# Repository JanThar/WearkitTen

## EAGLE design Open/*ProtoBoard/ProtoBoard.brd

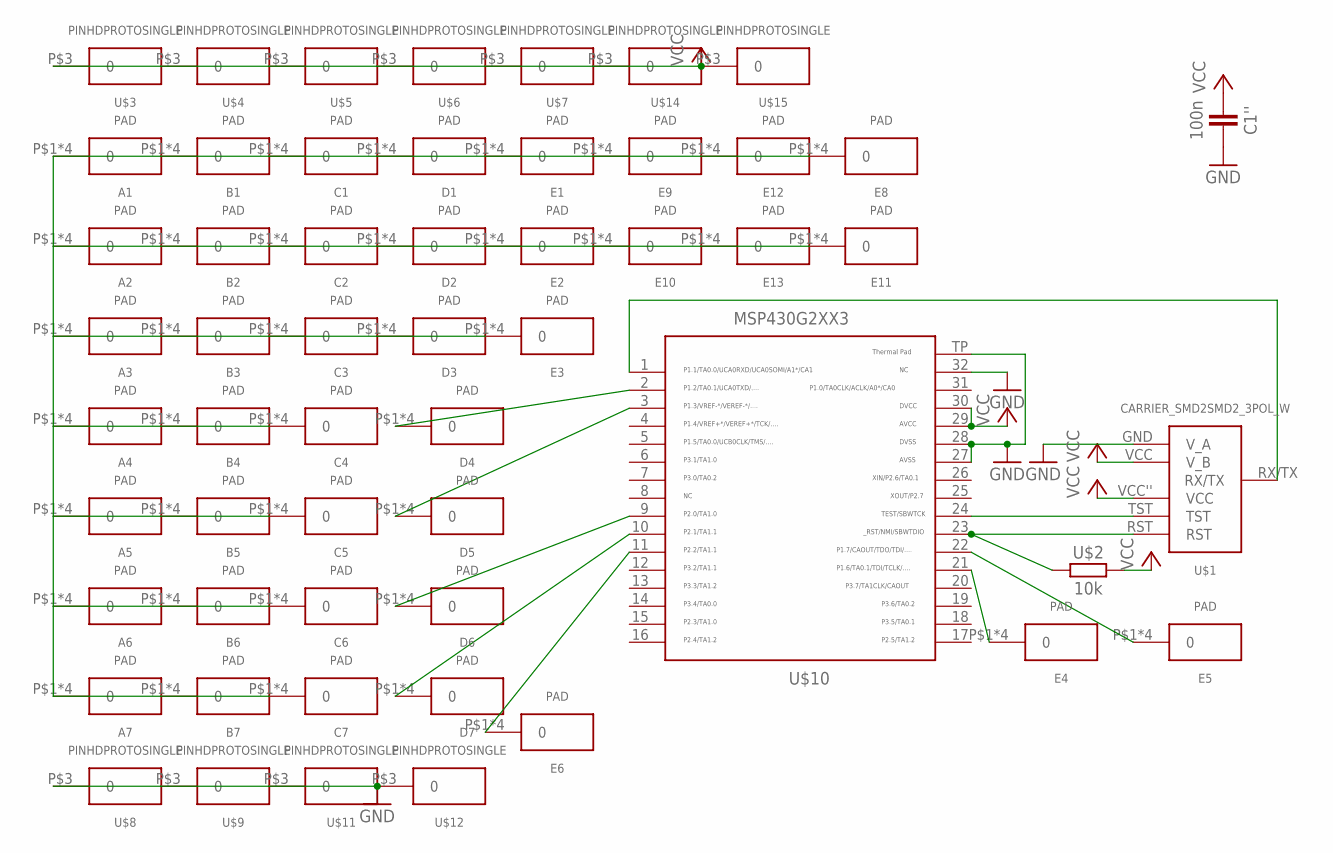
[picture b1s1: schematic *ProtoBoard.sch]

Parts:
A1, A2, A3, A4, A5, A6, A7: PAD; PROTPAD
B1, B2, B3, B4, B5, B6, B7: PAD; PROTPAD
C1, C2, C3, C4, C5, C6, C7: PAD; PROTPAD
C1'': 100n; 603
D1, D2, D3, D4, D5, D6, D7: PAD; PROTPAD
E1, E2, E3, E4, E5, E6, E8, E9, E10, E11, E12, E13: PAD; PROTPAD
U$1: CARRIER_SMD2SMD2_3POL_W; CARRIER_SMD2_WIDE_3POL
U$2: 10k; 603
U$3, U$4, U$5, U$6, U$7, U$8, U$9, U$11, U$12, U$14, U$15: PINHDPROTOSINGLE; PROTOPADSINGLE
U$10: MSP430G2553; QFN32

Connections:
GND: C1''.2, U$1.GND (V_A), U$8.P$3, U$9.P$3, U$10.27, U$10.28, U$10.32, U$10.TP, U$11.P$3, U$12.P$3
unnamed: A1.P$1, A1.P$2, A1.P$3, A1.P$4, A2.P$1, A2.P$2, A2.P$3, A2.P$4, A3.P$1, A3.P$2, A3.P$3, A3.P$4, A4.P$1, A4.P$2, A4.P$3, A4.P$4, A5.P$1, A5.P$2, A5.P$3, A5.P$4, A6.P$1, A6.P$2, A6.P$3, A6.P$4, A7.P$1, A7.P$2, A7.P$3, A7.P$4, B1.P$1, B1.P$2, B1.P$3, B1.P$4, B2.P$1, B2.P$2, B2.P$3, B2.P$4, B3.P$1, B3.P$2, B3.P$3, B3.P$4, B4.P$1, B4.P$2, B4.P$3, B4.P$4, B5.P$1, B5.P$2, B5.P$3, B5.P$4, B6.P$1, B6.P$2, B6.P$3, B6.P$4, B7.P$1, B7.P$2, B7.P$3, B7.P$4, C1.P$1, C1.P$2, C1.P$3, C1.P$4, C2.P$1, C2.P$2, C2.P$3, C2.P$4, C3.P$1, C3.P$2, C3.P$3, C3.P$4, C4.P$1, C4.P$2, C4.P$3, C4.P$4, C5.P$1, C5.P$2, C5.P$3, C5.P$4, C6.P$1, C6.P$2, C6.P$3, C6.P$4, C7.P$1, C7.P$2, C7.P$3, C7.P$4, D1.P$1, D1.P$2, D1.P$3, D1.P$4, D2.P$1, D2.P$2, D2.P$3, D2.P$4, D3.P$1, D3.P$2, D3.P$3, D3.P$4, E1.P$1, E1.P$2, E1.P$3, E1.P$4, E2.P$1, E2.P$2, E2.P$3, E2.P$4, E3.P$1, E3.P$2, E3.P$3, E3.P$4, E8.P$1, E8.P$2, E8.P$3, E8.P$4, E9.P$1, E9.P$2, E9.P$3, E9.P$4, E10.P$1, E10.P$2, E10.P$3, E10.P$4, E11.P$1, E11.P$2, E11.P$3, E11.P$4, E12.P$1, E12.P$2, E12.P$3, E12.P$4, E13.P$1, E13.P$2, E13.P$3, E13.P$4
unnamed: U$1.TST, U$10.24
unnamed: U$1.RST, U$2.1, U$10.23
unnamed: D4.P$1, D4.P$2, D4.P$3, D4.P$4, U$10.2
unnamed: D5.P$1, D5.P$2, D5.P$3, D5.P$4, U$10.3
unnamed: E5.P$1, E5.P$2, E5.P$3, E5.P$4, U$10.22
unnamed: E4.P$1, E4.P$2, E4.P$3, E4.P$4, U$10.21
unnamed: U$1.RX/TX, U$10.1
unnamed: D6.P$1, D6.P$2, D6.P$3, D6.P$4, U$10.9
unnamed: D7.P$1, D7.P$2, D7.P$3, D7.P$4, U$10.10
unnamed: E6.P$1, E6.P$2, E6.P$3, E6.P$4, U$10.11
VCC: C1''.1, U$1.VCC (V_B), U$1.VCC'' (VCC), U$2.2, U$3.P$3, U$4.P$3, U$5.P$3, U$6.P$3, U$7.P$3, U$10.29, U$10.30, U$14.P$3, U$15.P$3

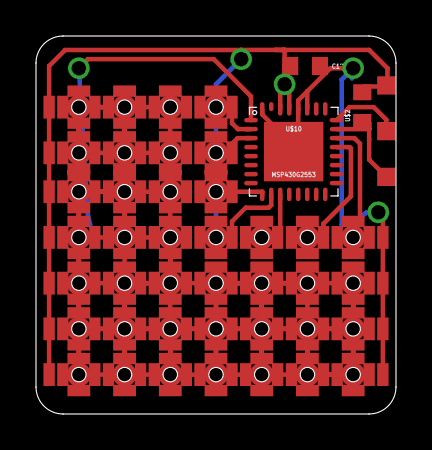
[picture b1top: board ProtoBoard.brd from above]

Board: 2 copper layers, 20.0 x 21.0 mm, 55 parts (0 on the bottom side), 13 nets.

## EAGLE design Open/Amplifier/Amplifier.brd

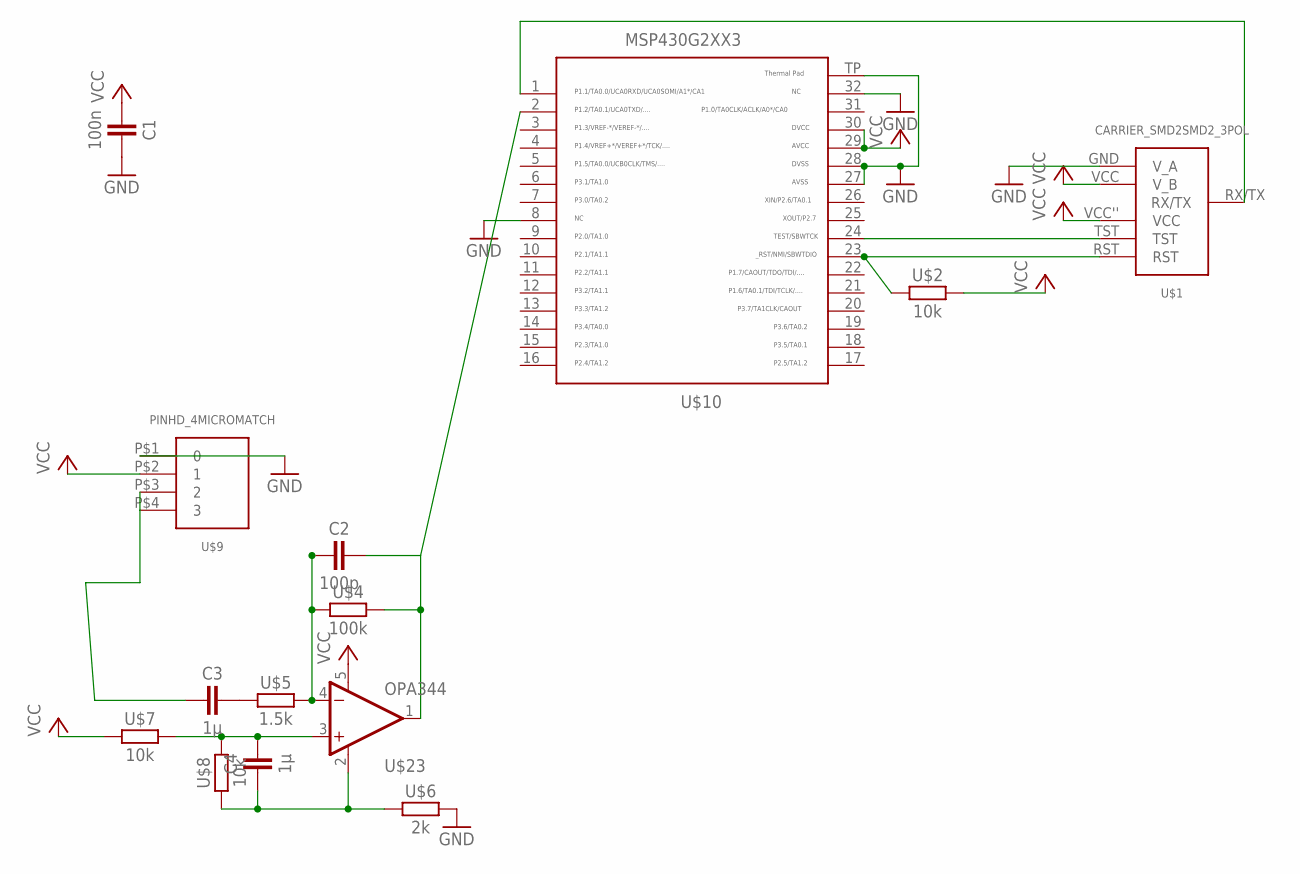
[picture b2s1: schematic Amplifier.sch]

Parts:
C1: 100n; 603
C2: 100p; 603
C3, C4: 1µ; 603
U$1: CARRIER_SMD2SMD2_3POL; CARRIER_SMD2_3POL
U$2, U$7, U$8: 10k; 603
U$4: 100k; 603
U$5: 1.5k; 603
U$6: 2k; 603
U$9: PINHD_4MICROMATCH; MICROMATCH4P0L
U$10: MSP430G2553; QFN32
U$23: OPA344; SOT23-5

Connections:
GND: C1.2, U$1.GND (V_A), U$6.2, U$9.P$1 (0), U$10.8, U$10.27, U$10.28, U$10.32, U$10.TP
unnamed: U$1.TST, U$10.24
unnamed: U$1.RST, U$2.1, U$10.23
unnamed: U$1.RX/TX, U$10.1
unnamed: C2.1, U$4.1, U$5.2, U$23.4 (-IN)
unnamed: C3.2, U$5.1
unnamed: C4.1, U$6.1, U$8.1, U$23.2 (V-)
unnamed: C3.1, U$9.P$3 (2), U$9.P$4 (3)
unnamed: C4.2, U$7.2, U$8.2, U$23.3 (+IN)
SOUND: C2.2, U$4.2, U$10.2, U$23.1 (OUT)
VCC: C1.1, U$1.VCC (V_B), U$1.VCC'' (VCC), U$2.2, U$7.1, U$9.P$2 (1), U$10.29, U$10.30, U$23.5 (V+)

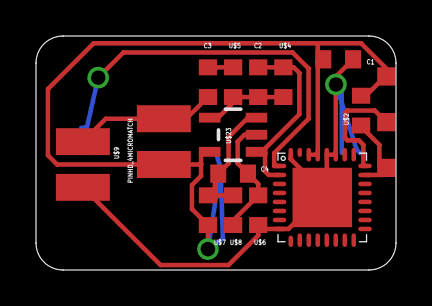
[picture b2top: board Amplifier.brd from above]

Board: 2 copper layers, 20.0 x 13.0 mm, 14 parts (0 on the bottom side), 11 nets.

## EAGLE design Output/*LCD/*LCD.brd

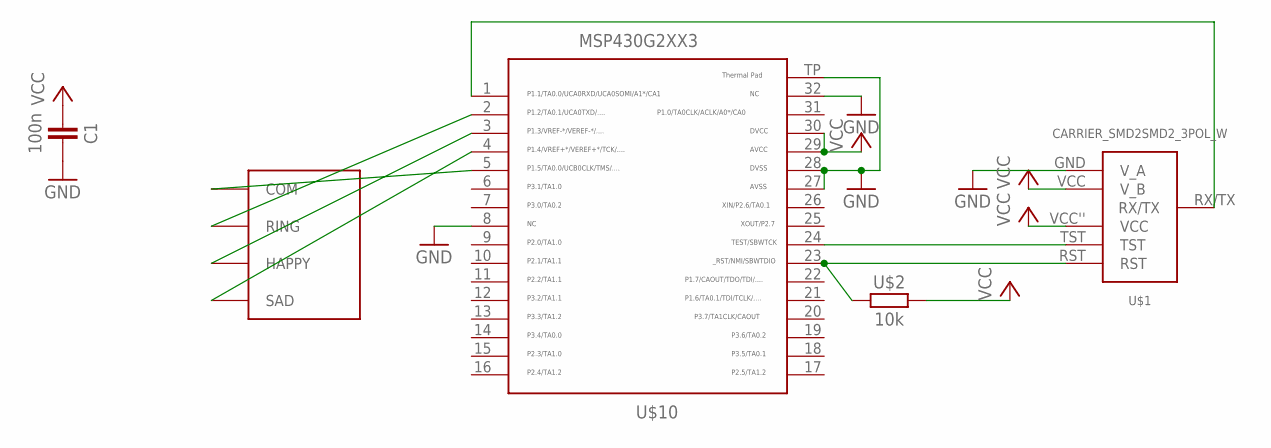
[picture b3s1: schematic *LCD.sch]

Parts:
C1: 100n; 603
U$1: CARRIER_SMD2SMD2_3POL_W; CARRIER_SMD2_WIDE_3POL
U$2: 10k; 603
U$3: SMILEY
U$10: MSP430G2553; QFN32

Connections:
GND: C1.2, U$1.GND (V_A), U$10.8, U$10.27, U$10.28, U$10.32, U$10.TP
unnamed: U$3.1 (COM), U$10.5
unnamed: U$1.TST, U$10.24
unnamed: U$1.RST, U$2.1, U$10.23
unnamed: U$3.2 (SAD), U$10.4
unnamed: U$3.3 (HAPPY), U$10.3
unnamed: U$3.4 (RING), U$10.2
unnamed: U$1.RX/TX, U$10.1
VCC: C1.1, U$1.VCC (V_B), U$1.VCC'' (VCC), U$2.2, U$10.29, U$10.30

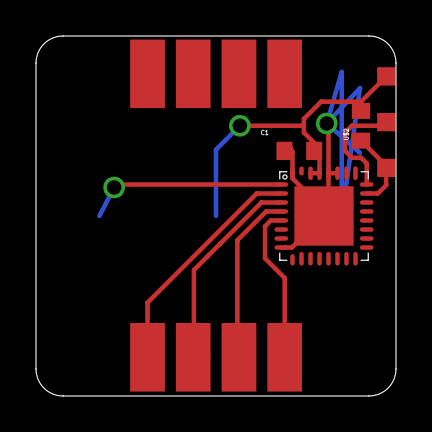
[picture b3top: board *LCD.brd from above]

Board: 2 copper layers, 20.0 x 20.0 mm, 5 parts (0 on the bottom side), 9 nets.

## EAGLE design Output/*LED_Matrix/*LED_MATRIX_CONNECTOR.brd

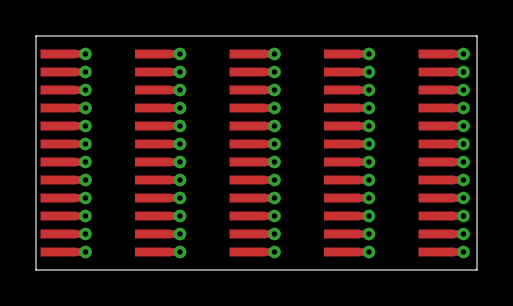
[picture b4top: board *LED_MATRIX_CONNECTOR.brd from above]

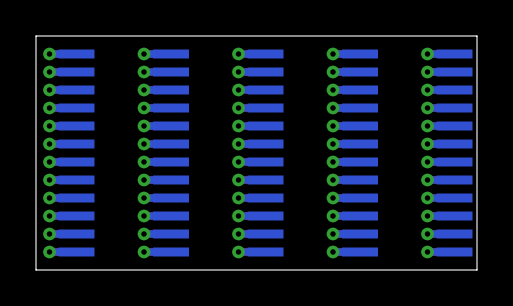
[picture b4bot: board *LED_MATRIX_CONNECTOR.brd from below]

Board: 2 copper layers, 24.5 x 13.0 mm, 10 parts (5 on the bottom side), 60 nets.

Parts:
U$1, U$2, U$3, U$4, U$5, U$6, U$7, U$8, U$9, U$10: PINHD_12FFC_1MM; FFC_1MM

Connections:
unnamed: U$1.P$1, U$2.P$1
unnamed: U$1.P$2, U$2.P$2
unnamed: U$1.P$3, U$2.P$3
unnamed: U$1.P$4, U$2.P$4
unnamed: U$1.P$5, U$2.P$5
unnamed: U$1.P$6, U$2.P$6
unnamed: U$1.P$7, U$2.P$7
unnamed: U$1.P$8, U$2.P$8
unnamed: U$1.P$9, U$2.P$9
unnamed: U$1.P$10, U$2.P$10
unnamed: U$1.P$11, U$2.P$11
unnamed: U$1.P$12, U$2.P$12
unnamed: U$3.P$1, U$4.P$1
unnamed: U$3.P$2, U$4.P$2
unnamed: U$3.P$3, U$4.P$3
unnamed: U$3.P$4, U$4.P$4
unnamed: U$3.P$5, U$4.P$5
unnamed: U$3.P$6, U$4.P$6
unnamed: U$3.P$7, U$4.P$7
unnamed: U$3.P$8, U$4.P$8
unnamed: U$3.P$9, U$4.P$9
unnamed: U$3.P$10, U$4.P$10
unnamed: U$3.P$11, U$4.P$11
unnamed: U$3.P$12, U$4.P$12
unnamed: U$5.P$1, U$6.P$1
unnamed: U$5.P$2, U$6.P$2
unnamed: U$5.P$3, U$6.P$3
unnamed: U$5.P$4, U$6.P$4
unnamed: U$5.P$5, U$6.P$5
unnamed: U$5.P$6, U$6.P$6
unnamed: U$5.P$7, U$6.P$7
unnamed: U$5.P$8, U$6.P$8
unnamed: U$5.P$9, U$6.P$9
unnamed: U$5.P$10, U$6.P$10
unnamed: U$5.P$11, U$6.P$11
unnamed: U$5.P$12, U$6.P$12
unnamed: U$7.P$1, U$8.P$1
unnamed: U$7.P$2, U$8.P$2
unnamed: U$7.P$3, U$8.P$3
unnamed: U$7.P$4, U$8.P$4
unnamed: U$7.P$5, U$8.P$5
unnamed: U$7.P$6, U$8.P$6
unnamed: U$7.P$7, U$8.P$7
unnamed: U$7.P$8, U$8.P$8
unnamed: U$7.P$9, U$8.P$9
unnamed: U$7.P$10, U$8.P$10
unnamed: U$7.P$11, U$8.P$11
unnamed: U$7.P$12, U$8.P$12
unnamed: U$9.P$1, U$10.P$1
unnamed: U$9.P$2, U$10.P$2
unnamed: U$9.P$3, U$10.P$3
unnamed: U$9.P$4, U$10.P$4
unnamed: U$9.P$5, U$10.P$5
unnamed: U$9.P$6, U$10.P$6
unnamed: U$9.P$7, U$10.P$7
unnamed: U$9.P$8, U$10.P$8
unnamed: U$9.P$9, U$10.P$9
unnamed: U$9.P$10, U$10.P$10
unnamed: U$9.P$11, U$10.P$11
unnamed: U$9.P$12, U$10.P$12

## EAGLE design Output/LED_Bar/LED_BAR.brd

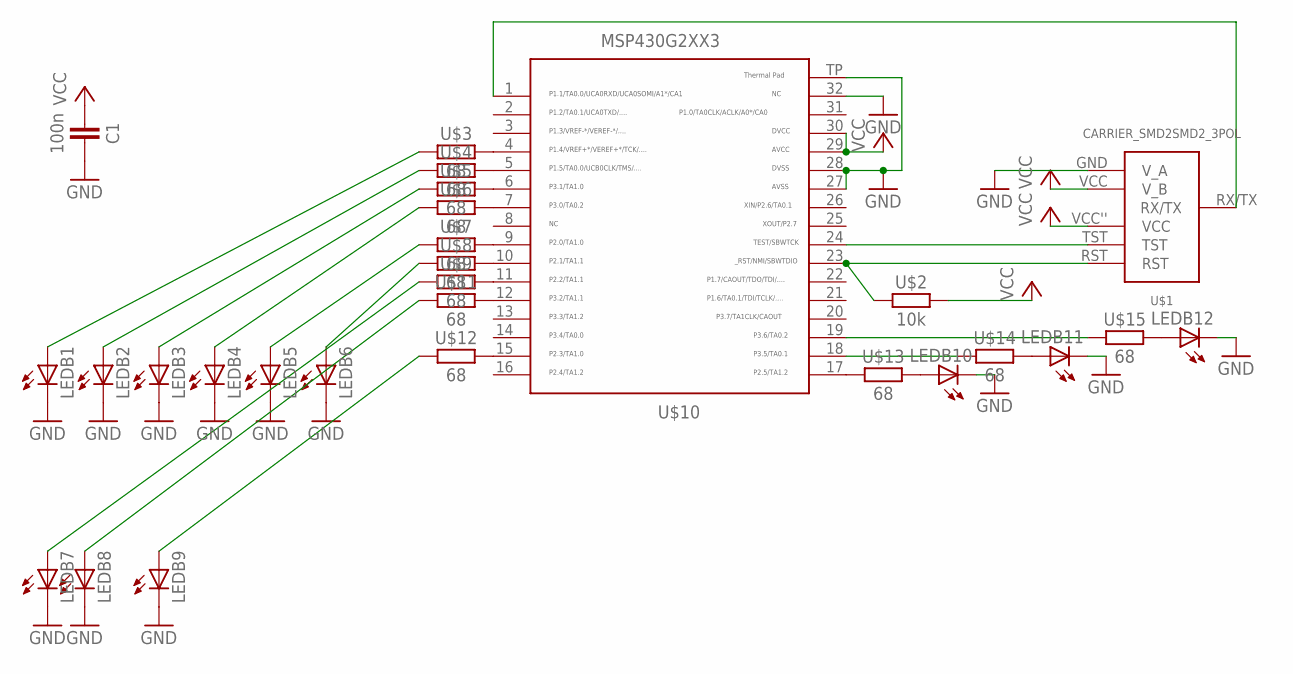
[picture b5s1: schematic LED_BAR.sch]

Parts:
C1: 100n; 603
LEDB1, LEDB2, LEDB3, LEDB4, LEDB5, LEDB6, LEDB7, LEDB8, LEDB9, LEDB10, LEDB11, LEDB12: LEDCHIPLED_0603; CHIPLED_0603
U$1: CARRIER_SMD2SMD2_3POL; CARRIER_SMD2_3POL
U$2: 10k; 603
U$3, U$4, U$5, U$6, U$7, U$8, U$9, U$11, U$12, U$13, U$14, U$15: 68; 603
U$10: MSP430G2553; QFN32

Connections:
GND: C1.2, LEDB1.C, LEDB2.C, LEDB3.C, LEDB4.C, LEDB5.C, LEDB6.C, LEDB7.C, LEDB8.C, LEDB9.C, LEDB10.C, LEDB11.C, LEDB12.C, U$1.GND (V_A), U$10.27, U$10.28, U$10.32, U$10.TP
unnamed: U$1.TST, U$10.24
unnamed: U$1.RST, U$2.1, U$10.23
unnamed: LEDB1.A, U$3.1
unnamed: LEDB2.A, U$4.1
unnamed: LEDB3.A, U$5.1
unnamed: U$3.2, U$10.4
unnamed: U$1.RX/TX, U$10.1
unnamed: LEDB4.A, U$6.1
unnamed: LEDB5.A, U$7.1
unnamed: LEDB6.A, U$8.1
unnamed: U$4.2, U$10.5
unnamed: LEDB7.A, U$9.1
unnamed: LEDB8.A, U$11.1
unnamed: LEDB9.A, U$12.1
unnamed: U$5.2, U$10.6
unnamed: U$6.2, U$10.7
unnamed: U$7.2, U$10.9
unnamed: U$10.19, U$15.1
unnamed: U$10.18, U$14.1
unnamed: U$8.2, U$10.10
unnamed: U$9.2, U$10.11
unnamed: U$10.15, U$12.2
unnamed: U$10.17, U$13.1
unnamed: LEDB10.A, U$13.2
unnamed: LEDB11.A, U$14.2
unnamed: LEDB12.A, U$15.2
unnamed: U$10.12, U$11.2
VCC: C1.1, U$1.VCC (V_B), U$1.VCC'' (VCC), U$2.2, U$10.29, U$10.30

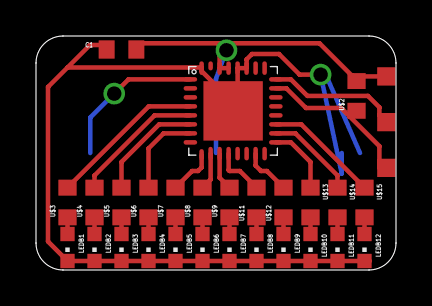
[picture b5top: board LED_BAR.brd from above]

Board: 2 copper layers, 20.0 x 13.0 mm, 28 parts (0 on the bottom side), 29 nets.

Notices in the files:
parts and their libraries:
SparkFun-AnalogIC: Licensing: CC v3.0 Share-Alike You are welcome to use this library for commercial purposes.
